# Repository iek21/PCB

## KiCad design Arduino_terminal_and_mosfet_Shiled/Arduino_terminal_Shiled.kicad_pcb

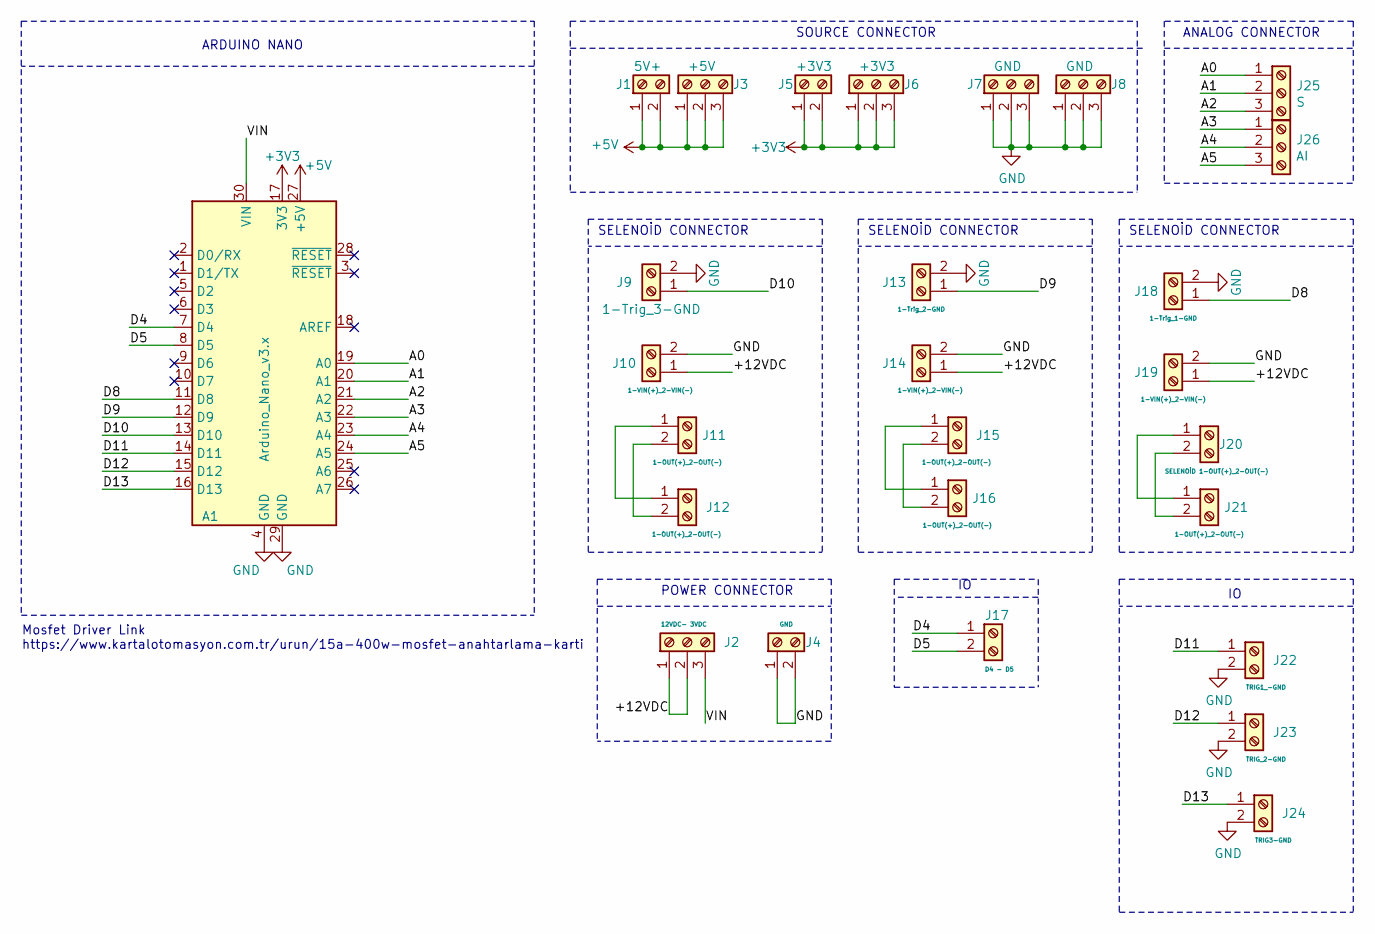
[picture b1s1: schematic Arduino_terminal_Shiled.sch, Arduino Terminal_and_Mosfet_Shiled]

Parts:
A1: Arduino_Nano_v3.x; Arduino_Nano
J1: 5V+; Altech_AK300_1x02_P5.00mm_45-Degree
J2: 12VDC- 3VDC; Altech_AK300_1x03_P5.00mm_45-Degree
J3: +5V; Altech_AK300_1x03_P5.00mm_45-Degree
J4: GND; Altech_AK300_1x02_P5.00mm_45-Degree
J5: +3V3; Altech_AK300_1x02_P5.00mm_45-Degree
J6: +3V3; Altech_AK300_1x03_P5.00mm_45-Degree
J7, J8: GND; Altech_AK300_1x03_P5.00mm_45-Degree
J9: 1-Trig_3-GND; TerminalBlock_Philmore_TB132_1x02_P5.00mm_Horizontal
J10, J14, J19: 1-VIN(+)_2-VIN(-); TerminalBlock_Philmore_TB132_1x02_P5.00mm_Horizontal
J11, J16, J21: 1-OUT(+)_2-OUT(-); TerminalBlock_Philmore_TB132_1x02_P5.00mm_Horizontal
J12, J15: 1-OUT(+)_2-OUT(-); Altech_AK300_1x02_P5.00mm_45-Degree
J13: 1-Trig_2-GND; TerminalBlock_Philmore_TB132_1x02_P5.00mm_Horizontal
J17: D4 - D5; Altech_AK300_1x02_P5.00mm_45-Degree
J18: 1-Trig_1-GND; TerminalBlock_Philmore_TB132_1x02_P5.00mm_Horizontal
J20: SELENOİD 1-OUT(+)_2-OUT(-); Altech_AK300_1x02_P5.00mm_45-Degree
J22: TRIG1_-GND; Altech_AK300_1x02_P5.00mm_45-Degree
J23: TRIG_2-GND; Altech_AK300_1x02_P5.00mm_45-Degree
J24: TRIG3-GND; Altech_AK300_1x02_P5.00mm_45-Degree
J25: S; Altech_AK300_1x03_P5.00mm_45-Degree
J26: AI; Altech_AK300_1x03_P5.00mm_45-Degree

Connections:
+3V3: A1.17 (3V3), J5.1, J5.2, J6.1, J6.2, J6.3
+5V: A1.27 (+5V), J1.1, J1.2, J3.1, J3.2, J3.3
/+12VDC: J2.1, J2.2, J10.1, J14.1, J19.1
/A0: A1.19 (A0), J25.1
/A1: A1.20 (A1), J25.2
/A2: A1.21 (A2), J25.3
/A3: A1.22 (A3), J26.1
/A4: A1.23 (A4), J26.2
/A5: A1.24 (A5), J26.3
/D4: A1.7 (D4), J17.1
/D5: A1.8 (D5), J17.2
/D8: A1.11 (D8), J18.1
/D9: A1.12 (D9), J13.1
/D10: A1.13 (D10), J9.1
/D11: A1.14 (D11), J22.1
/D12: A1.15 (D12), J23.1
/D13: A1.16 (D13), J24.1
/VIN: A1.30 (VIN), J2.3
GND: A1.4 (GND), A1.29 (GND), J4.1, J4.2, J7.1, J7.2, J7.3, J8.1, J8.2, J8.3, J9.2, J10.2, J13.2, J14.2, J18.2, J19.2, J22.2, J23.2, J24.2
unnamed: J11.1, J12.1
unnamed: J11.2, J12.2
unnamed: J15.1, J16.1
unnamed: J15.2, J16.2
unnamed: J20.1, J21.1
unnamed: J20.2, J21.2

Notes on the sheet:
ANALOG CONNECTOR
SOURCE CONNECTOR
SELENOİD CONNECTOR
POWER CONNECTOR
ARDUINO NANO
Mosfet Driver Link https://www.kartalotomasyon.com.tr/urun/15a-400w-mosfet-anahtarlama-karti

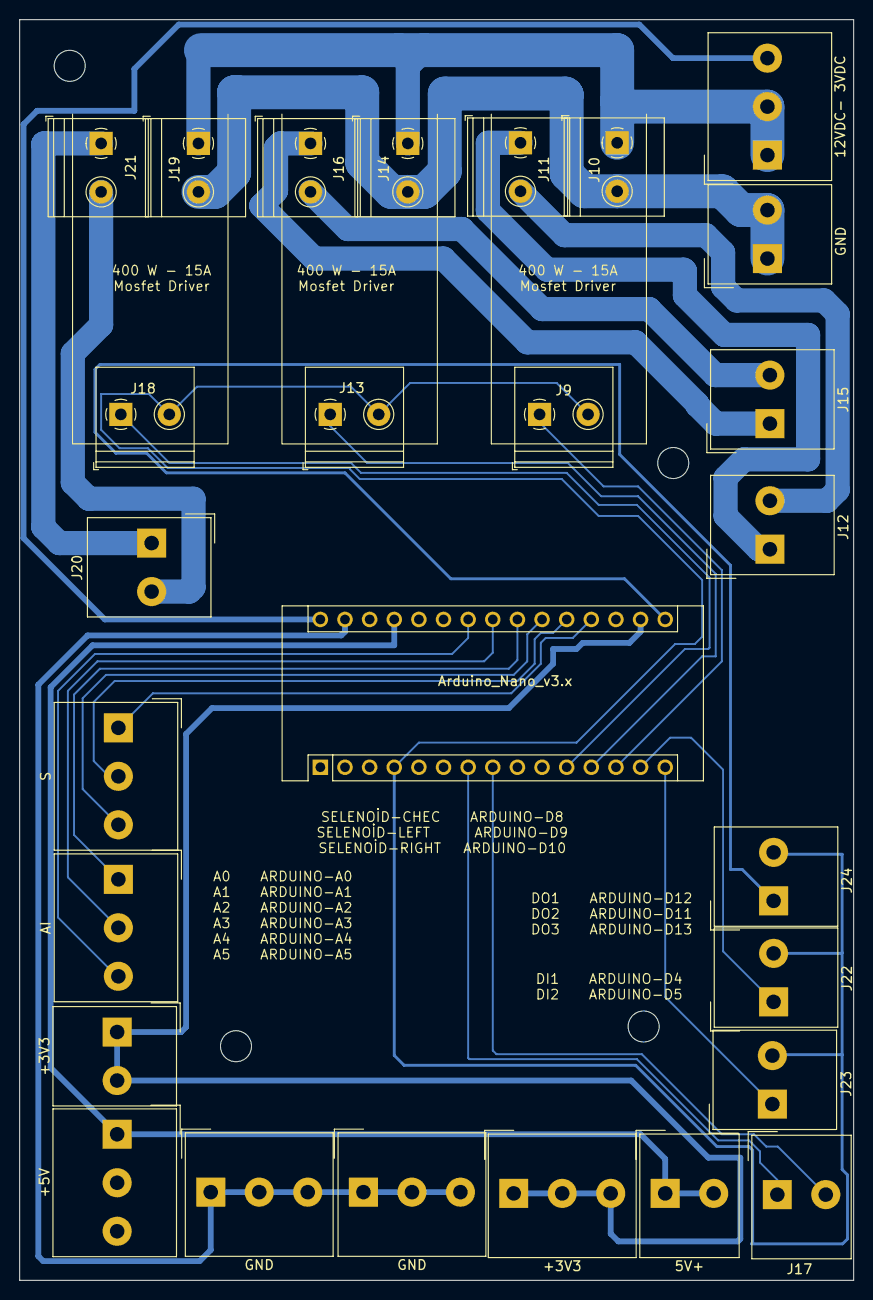
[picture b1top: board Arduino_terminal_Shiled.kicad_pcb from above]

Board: 2 copper layers, 86.0 x 130.0 mm, 31 parts (0 on the bottom side), 25 nets.

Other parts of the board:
HLE1: HOLE1; MountingHole_3.2mm_M3
HLE2: HOLE2; MountingHole_3.2mm_M3
HLE3: HOLE3; MountingHole_3.2mm_M3
HLE4: HOLE4; MountingHole_3.2mm_M3

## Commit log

2021-09-27 Add files via upload
    AltiumDesigner
